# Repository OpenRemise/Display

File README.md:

### Housing and Display for Open remise 
Housing will be the basic for the Display Dimensions. 
The Gcode for the Housing and the Display Cover must generated local
according to the used 3d Printer

Display Software runnig on Arduino added  including Small OLED Display

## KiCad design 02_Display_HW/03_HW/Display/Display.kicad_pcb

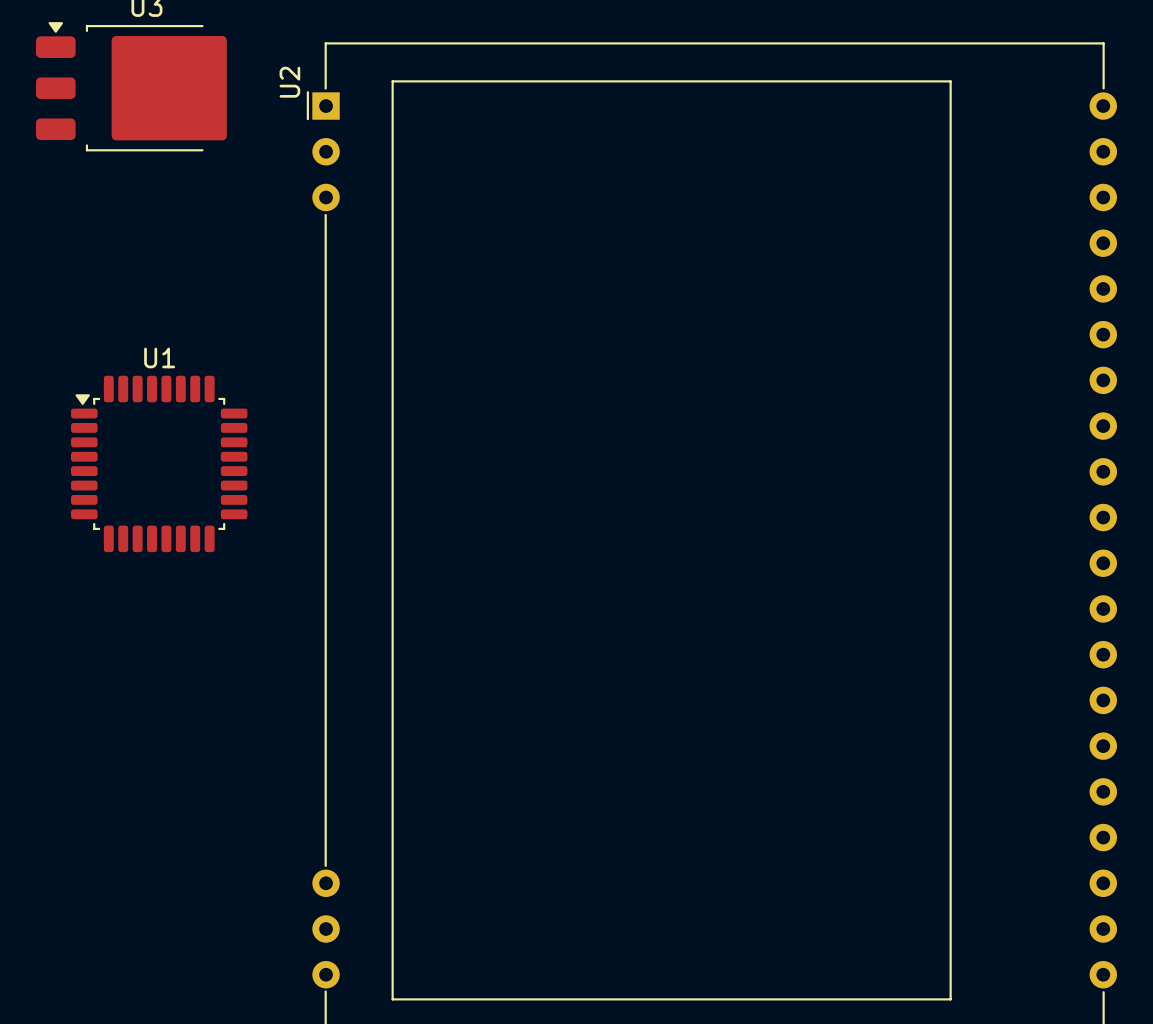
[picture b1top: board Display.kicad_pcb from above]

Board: 2 copper layers, 3 parts (0 on the bottom side), 5 nets, no tracks yet.

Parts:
U1: ATmega328P-A; TQFP-32_7x7mm_P0.8mm
U2: EA_DOGM128X-6; EA_DOGM128-6
U3: AMS1117CD-3.3; TO-252-3_TabPin2

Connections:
unnamed: U1.3 (GND), U1.5 (GND), U1.21 (GND)
unnamed: U1.4 (VCC), U1.6 (VCC)
unnamed: U1.29 (~RESET/PC6), U2.39 (~RST)
unnamed: U2.34 (VDD2), U2.35 (VDD)
unnamed: U2.26 (VSS), U2.33 (VSS)

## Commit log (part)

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2025-12-30 Add initial README with project display information
2025-12-30 Update README with housing and display information
    Added details about housing and display dimensions for Open remise.
2025-12-30 Initial set up
    feat:#1
2025-12-30 Update Lastenheft.odt documentation
    Revised the Lastenheft.odt file in the documentation folder. Changes include updated requirements or specifications.
    feat: #2
2025-12-30 Add Deckel.FCStd CAD file
    Added a new FreeCAD file 'Deckel.FCStd' to the Display/02_Cad directory. This file likely contains CAD data for a component Deckel. with Displa An button Cutouts . Draft version
    feat: #3
2026-01-02 Strating Dispaly HW
    Feat: #4
2026-01-02 Update .gitignore
    Add The backup folder from Kicad
2026-01-04 Reorganise Buttons in CPP
    to do
    Funktion from Read in to Update ()
2026-01-04 Create c_cpp_properties.json
    update of VS code
2026-01-04 Initial Ideas on display
    frist ideas of Display no real code
2026-01-04 MAIN first ideas
    first Main ideas no real code
2026-01-04 Protokoll first ideas
    no real code
    First ideas
2026-01-07 Restructur Projekt
    feat : #1
2026-01-07 renaming folder
    feat : #1
2026-01-09 Delete protokoll.h
    feat: #5
2026-01-30 Update .gitignore
    exclude local test software.
2026-01-30 cleanup folder
    deleted files
2026-01-30 Implement button logic, ctor, and SetLED
    Add Buttons() constructor and a SetLED() method, initialize a Button state member, and implement button state handling in update(). The changes add press/hold detection, timers, and a 5s reset sequen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
2026-01-30 Implement U8g2 display class and screens
    Replace include-guard with pragma once and add required headers (Arduino, U8g2, Wire, Logo.h). Add U8G2_SH1107 display member and constructor to initialize the driver object. Implement begin() to per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
2026-01-30 Add Logo.h with display bitmap arrays
    Introduce Openremise_Display/include/Logo.h defining PROGMEM bitmap arrays for display logos (openeremise_logo_100_32 and a sample placeholder sample_logo_96_96). The header includes pragma once and 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
2026-01-30 Simplify main.cpp initialization and loop
    Replace the old SYS-based startup and task framework with direct initialization of display and buttons. Added Wire.h and instantiated OpenRemiseDisplay and Buttons; setup() now starts Serial, initial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
2026-01-30 Update logo bitmap and display call
    Replace the old 100x32 PROGMEM logo with a new 103x21 bitmap (openeremise_logo_103_21) and update the drawXBMP call in ShowWelcome() to use the new dimensions and symbol. The header array and bitmap 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
2026-02-01 Update Logo.h
    Update für ! bit daten Xbmp
2026-02-01 Refactor main.h and setup/protokoll integration
    Replace include-guard with #pragma once; remove legacy mode/error #defines and unused Learnsatus, add PROTOKOLL RX/TX pin defines. Restructure SYS to include Error_Code and timestamps, introduce Mode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
2026-02-01 Refactor Protokoll class for Stream-based JSON
    Introduce Stream-based Protokoll API and basic JSON parsing flow. Changes include: add OpenRemiseProtokoll(Stream& transport) constructor and store Stream pointer; move to ArduinoJson include and adj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
2026-02-01 Initialize Button member in constructor
    Set the Button member to NO_BUTTONS in Buttons::Buttons() to ensure a defined default state and avoid potential uninitialized-variable issues. This adds an explicit initialization in Openremise_Displ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
2026-02-05 Add screen getter and invalid start state
    Introduce SCREEN_INVALID enum and implement get_Current_Screen() to expose the current screen ID. Initialize the display by setting current screen to SCREEN_INVALID to force the first update, and mak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
2026-02-05 Refactor pin defs, init flow, and button handling
    Rework hardware pin assignments and startup logic: remapped button/LED pins and added commented I2C pin refs; set SYS state and error code earlier in setup; moved and clarified Serial/Debug_port init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
2026-02-05 Temporarily disable JSON parsing and transport reads
    Comment out the serial/transport read loop in OpenRemiseProtokoll::update() and disable ArduinoJson usage in parseJson() (StaticJsonDocument, deserializeJson and example extraction lines). The origin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
2026-02-05 Add debounce/hold/reset defines and LED logic
    Introduce LED and button timing constants (LED_ON/LED_OFF, Button_DEBOUNCE_TIME, BUTTON_HOLD_TIME, BUTTON_RESET_TIME) and document LEDs as active LOW. Replace hardcoded initial LED writes and magic t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
2026-02-05 Display: add blink, title pos, I2C scanner
    Add configurable display helpers and blink support: introduce SCREEN_Title_x/Y and BLINKTIME defines and an optional I2C_SCANNER macro. Add optional I2C scan output in begin() (ifdef I2C_SCANNER), in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
2026-02-07 Add MISRA cppcheck pre-build check and docs
    feat: #7
    Introduce a pre-build MISRA check using cppcheck: add extra_scripts/Misra_check.py which runs cppcheck with the MISRA addon, writes reports/misra.csv, creates a .cppcheck build dir and fails the buil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
2026-02-07 Update display features, error handling, and init
    feat: #8
    Introduce display layout and control improvements, bug fixes, and init changes.
    - Add LOGO_x/LOGO_y defines and reposition logos across screens for consistent placement.
    - Add display state members: Display_error_string, Display_info_string, and initialize defaults in begin().
    - Extend API: set_error_code(uint8_t, const char*), set_info_string(const char*), and force_update() to allow setting error text and forcing redraws.
    - Improve blink handling: call toggleBlinkState() inside update(), mark screens for redraw when blinking, and tweak frame drawing for blinking/error screens.
2026-02-07 Add S3-related error codes to enum
    Introduce ERROR_S3_NO_WIFI and ERROR_S3_SHORTCUT into the ErrorCodes enum, move ERROR_UNKNOWN = 0xFF to the end, and add a small comment placeholder for system functions. These additions create disti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
    feat:#9
2026-02-07 Refactor Protokoll: add RX handling and timeout
    feat: #10
    Restructure OpenRemiseProtokoll to support streamed RX parsing and timeout handling. Changes include: add Protokoll_Data_error_t enum and data_controll_t struct; introduce RX buffer (rxBuffer, rxInde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
2026-02-07 Add Data_from_Stream struct and parse flow
    feat: #10
    Introduce Data_from_Stream_t and a global Data_from_Stream instance to hold parsed stream data (ip, state, rssi, voltage, current, track_state, valid). Refactor Protokoll class internals: add getData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
2026-02-10 Use bitmask error codes; tweak main loop behavior
    Change error enums to explicit bitmask values (ERROR_DISPLAY=0x01, ERROR_BUTTONS=0x02, ERROR_PROTOKOLL=0x04, ERROR_S3_NO_WIFI=0x10, ERROR_S3_SHORTCUT=0x20) to enable bitwise use. Move protokoll.begin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
2026-02-10 Extend Data_from_Stream and change JSON doc type
    Add error/info size defines and expand Data_from_Stream_t with network (ip, state, ssid, rssi), tracking fields, Status and error fields (Error_id, Error_text, Error_INFO). Remove the previous global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
2026-02-11 Refactor display screens and layout
    Introduce structured screen descriptors and layout constants, reorganize display data and rendering. Adds ScreenDescriptor array with static titles/labels, a Display_content_t for dynamic line conten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
    Not t
2026-02-11 Flag invalid display screen as error
    Add a check that sets SYS.Error_Code |= ERROR_DISPLAY when display.get_Current_Screen() == SCREEN_INVALID. This ensures the display invalid state is recorded in SYS.Error_Code and will be shown by th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
2026-02-22 Update Buttons.h
    Debounce time for Butten hold = 150 ms (500)
2026-02-22 Refactor display screens and content handling
    Introduce a richer ScreenId enum and add named line Y offsets; replace the old Content struct with a simple content[5] array and implement Set_Current_content to update it. Update Get_Current_Screen 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
2026-02-22 Refactor protokoll: manual impl, JSON map & parser
    Introduce PROTOKOLL_MANUAL to control inclusion of the implementation and split the implementation into a new Protokoll_2.cpp when manual mode is enabled. Update protokoll.h with new JSON key defines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
2026-02-22 Use data_controll.currentIdx for parsing
    Add currentIdx to data_controll_t and migrate parsing state to that member. Initialize currentIdx in begin() and reset when a new message starts, then use data_controll.currentIdx instead of a local 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
    feat: #5
    Software not finally tested HW issue with S§
2026-02-24 Show mDNS on network screen; refine blink update
    Replace the NETWORK screen's second label from "Status :" to "mDNS " to display mDNS info. In Display.cpp add/clarify blink handling by calling toggleBlinkState() and documenting that screens should 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
    feat: #10
2026-02-24 Init data buffers and harden JSON parser
    Openremise_Display: initialize data[] in begin() and strengthen JSON key/value parsing and flow control.
    - protokoll.h: minor whitespace/alignment fixes for JSON_* macros.
    - Protokoll_2.cpp: prefill data array for testing; guard getProtIndex against null keys; ignore '"' characters in keys and values; added logic to map keys to indices and skip unknown keys; improved s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
2026-02-25 Refactor display layout and remove ShowDisplay
    Update display geometry and clean up obsolete display code. Adjusted layout constants (SCREEN_FIXED_Y from 70->78, SCREEN_DATA_X from 50->45) and replaced hardcoded coordinates in ShowNormalMode with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
    feat: #18
2026-02-25 Refactor init and display update timing
    Adjust startup and runtime timing and improve display/update flow. Reduce SLEEP_TIMEOUT to 10s, add DISPLAY_UPDATE_INTERVAL and WAIT_TIME_STARTTIME constants, and use WAIT_TIME_STARTTIME for the init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
2026-02-25 Add contentChanged flag and tighten buffer sizes
    Introduce a contentChanged flag to track when incoming JSON values actually change so the display can update only when needed. Added Get_Content_Changed() and reset_Content_Changed() APIs and set/res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
    feat: #20
2026-02-26 Adjust sleep, display updates, and content mapping
    Increase SLEEP_TIMEOUT from 10000ms to 30000ms and tidy up display/LED logic. Remove redundant button LED calls, ensure SYS.time_stamp is updated when display changes, and call display.update() regul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
2026-02-26 Adjust display layout and blink/frame behavior
    Refine display layout constants and update drawing/blink logic. Centered SCREEN_Title_x and tweaked title/logo/data/fixed coordinates for better alignment. Clear the u8g2 buffer before drawing in Sho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
2026-02-26 Change JSON_STATUS value to 'state'
    Update protocol macro: JSON_STATUS now maps to "state" instead of "status" to reflect the updated JSON field name. Also adjusted the JSON_Service comment to indicate service mode ("Service mode POM//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
2026-02-26 Add MISRA compliance report CSV
    Add a new MISRA report (Openremise_Display/reports/misra.csv) produced by static analysis. The report lists issues to address: multiple uninitialized member variables in Buttons.cpp and Protokoll_2.c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
2026-02-26 Add RAM usage hints report
    Add Openremise_Display/reports/ram_usage_hints.txt: a RAM analysis and optimization guide (dated 26 Feb 2026) that identifies RAM hotspots and provides actionable recommendations. Covers global objec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
2026-03-03 Display: add SW version & refine startup/update
    Introduce SW_Version macro and display it when valid protocol data is available. Increase WAIT_TIME_STARTTIME from 5000 to 15000 ms to allow more time for startup data. In setup(), call protokoll.upd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
2026-03-03 Remove old protokoll.Cpp and tweak Protokoll_2.cpp
    Delete the obsolete Openremise_Display/src/Protokoll/protokoll.Cpp implementation file and consolidate implementation in Protokoll_2.cpp. In Protokoll_2.cpp adjust the test initialization string from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
2026-03-03 Add German project description
    Add 01_doc/Projektbeschreibung.md — a German-language overview of the Openremise_Display project. The new doc summarizes the Display, Main, Buttons and Protokoll modules and enumerates important #def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
